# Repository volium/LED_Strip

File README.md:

# LED_Strip
Simple LED strip (4S2P) to be driven by external constant current source

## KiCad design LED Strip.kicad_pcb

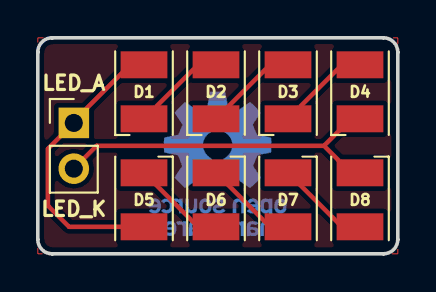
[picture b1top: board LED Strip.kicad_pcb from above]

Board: 2 copper layers, 20.0 x 12.0 mm, 10 parts (0 on the bottom side), 8 nets.

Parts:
D1, D2, D3, D4, D5, D6, D7, D8: LED; LED_PLCC-2
J1: CONN_01X02; Pin_Header_Straight_1x02_Pitch2.54mm
OSHW-Logo: OSHW-Logo_7.5x8mm_Copper

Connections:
/LED_A: D1.2, D5.2, J1.1
/LED_K: D4.1, D8.1, J1.2
unnamed: D1.1, D2.2
unnamed: D2.1, D3.2
unnamed: D3.1, D4.2
unnamed: D5.1, D6.2
unnamed: D6.1, D7.2
unnamed: D7.1, D8.2

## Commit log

2017-07-26 Adds project files
    Commits schematic, netlist and layout based on CLM3C
2017-07-26 Replaces LED_PLCC-2 packages with LED_0603
2017-07-26 Reduces overall footprint, cleans up placement of components and routes
2017-07-26 Adds copper pours to top and bottom layers
2017-07-26 Reduced size of board to 12 x 20 mm, redid some tracks
2017-07-26 Adds corner smoothing (0.05") to copper pours
2017-07-27 Adds project name and version to silkscreen Adds OSH logo to bottom copper layer Generated gerber files
2017-07-27 Adds project name, version and OSH logo
2017-07-27 Generated gerber files
2017-07-31 Updates 3D models for LEDs
    Updates 3D models for all LED_PLCC-2 LEDs to new AA3021.wrl in the 3DModels repository
